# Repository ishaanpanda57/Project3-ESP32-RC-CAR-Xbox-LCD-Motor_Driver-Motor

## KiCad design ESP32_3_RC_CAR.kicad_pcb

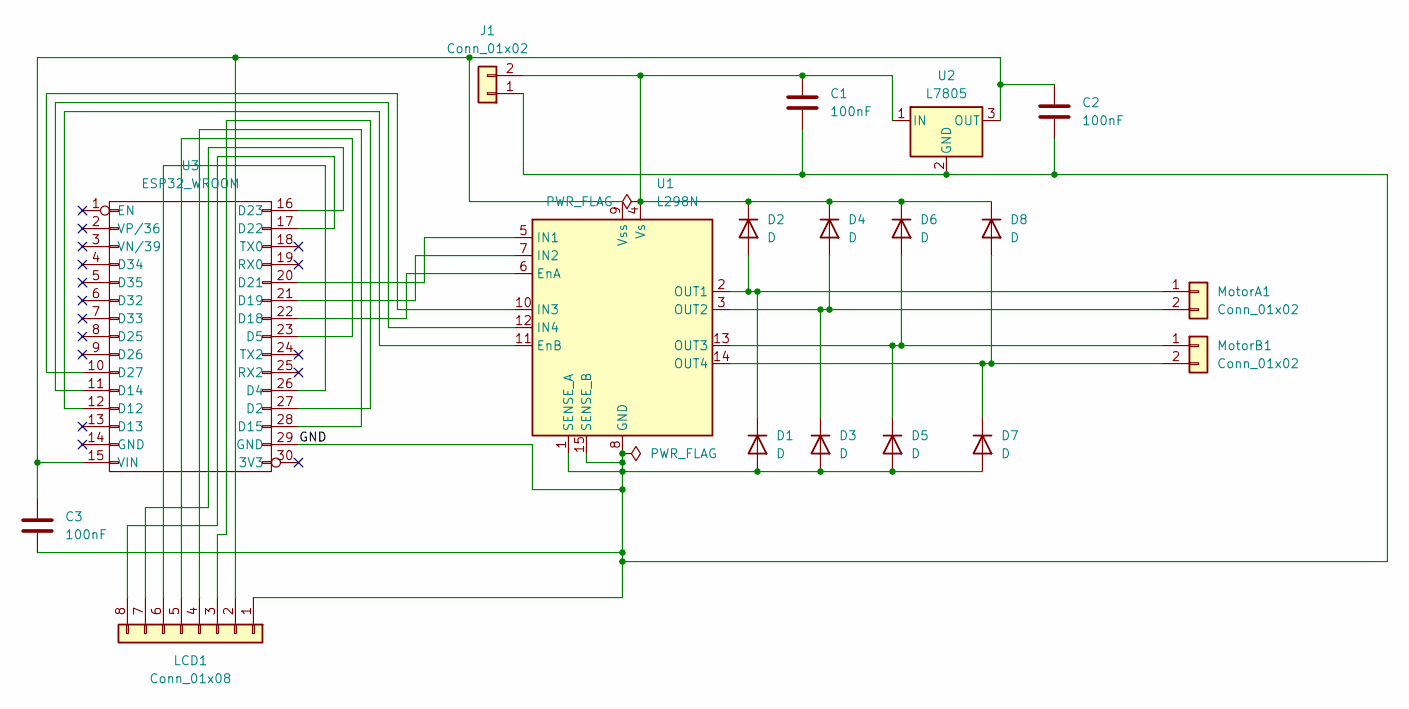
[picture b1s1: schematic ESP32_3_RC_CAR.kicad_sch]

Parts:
C1, C2, C3: 100nF; C_Disc_D3.0mm_W1.6mm_P2.50mm
D1, D2, D3, D4, D5, D6, D7, D8: D; D_DO-41_SOD81_P7.62mm_Horizontal
J1: Conn_01x02; PinHeader_1x02_P2.54mm_Vertical
LCD1: Conn_01x08; PinHeader_1x08_P2.54mm_Vertical
MotorA1: Conn_01x02; PinHeader_1x02_P2.54mm_Vertical
MotorB1: Conn_01x02; PinHeader_1x02_P2.54mm_Vertical
U1: L298N; TO-220-15_P2.54x2.54mm_StaggerEven_Lead5.84mm_TabDown
U2: L7805; TO-220-3_Horizontal_TabDown
U3: ESP32_WROOM; Footprint

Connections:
/GND: C1.2, C2.2, C3.2, D1.2 (A), D3.2 (A), D5.2 (A), D7.2 (A), J1.1, LCD1.1, U1.1 (SENSE_A), U1.8 (GND), U1.15 (SENSE_B), U2.2 (GND), U3.29 (GND)
unnamed: D1.1 (K), D2.2 (A), MotorA1.1, U1.2 (OUT1)
unnamed: C1.1, D2.1 (K), D4.1 (K), D6.1 (K), D8.1 (K), J1.2, U1.4 (Vs), U2.1 (IN)
unnamed: D3.1 (K), D4.2 (A), MotorA1.2, U1.3 (OUT2)
unnamed: D5.1 (K), D6.2 (A), MotorB1.1, U1.13 (OUT3)
unnamed: D7.1 (K), D8.2 (A), MotorB1.2, U1.14 (OUT4)
unnamed: C2.1, C3.1, LCD1.2, U1.9 (Vss), U2.3 (OUT), U3.15 (VIN)
unnamed: LCD1.3, U3.27 (D2)
unnamed: LCD1.4, U3.28 (D15)
unnamed: LCD1.5, U3.23 (D5)
unnamed: LCD1.6, U3.26 (D4)
unnamed: LCD1.7, U3.16 (D23)
unnamed: LCD1.8, U3.17 (D22)
unnamed: U1.6 (EnA), U3.22 (D18)
unnamed: U1.11 (EnB), U3.12 (D12)
unnamed: U1.5 (IN1), U3.20 (D21)
unnamed: U1.7 (IN2), U3.21 (D19)
unnamed: U1.10 (IN3), U3.10 (D27)
unnamed: U1.12 (IN4), U3.11 (D14)

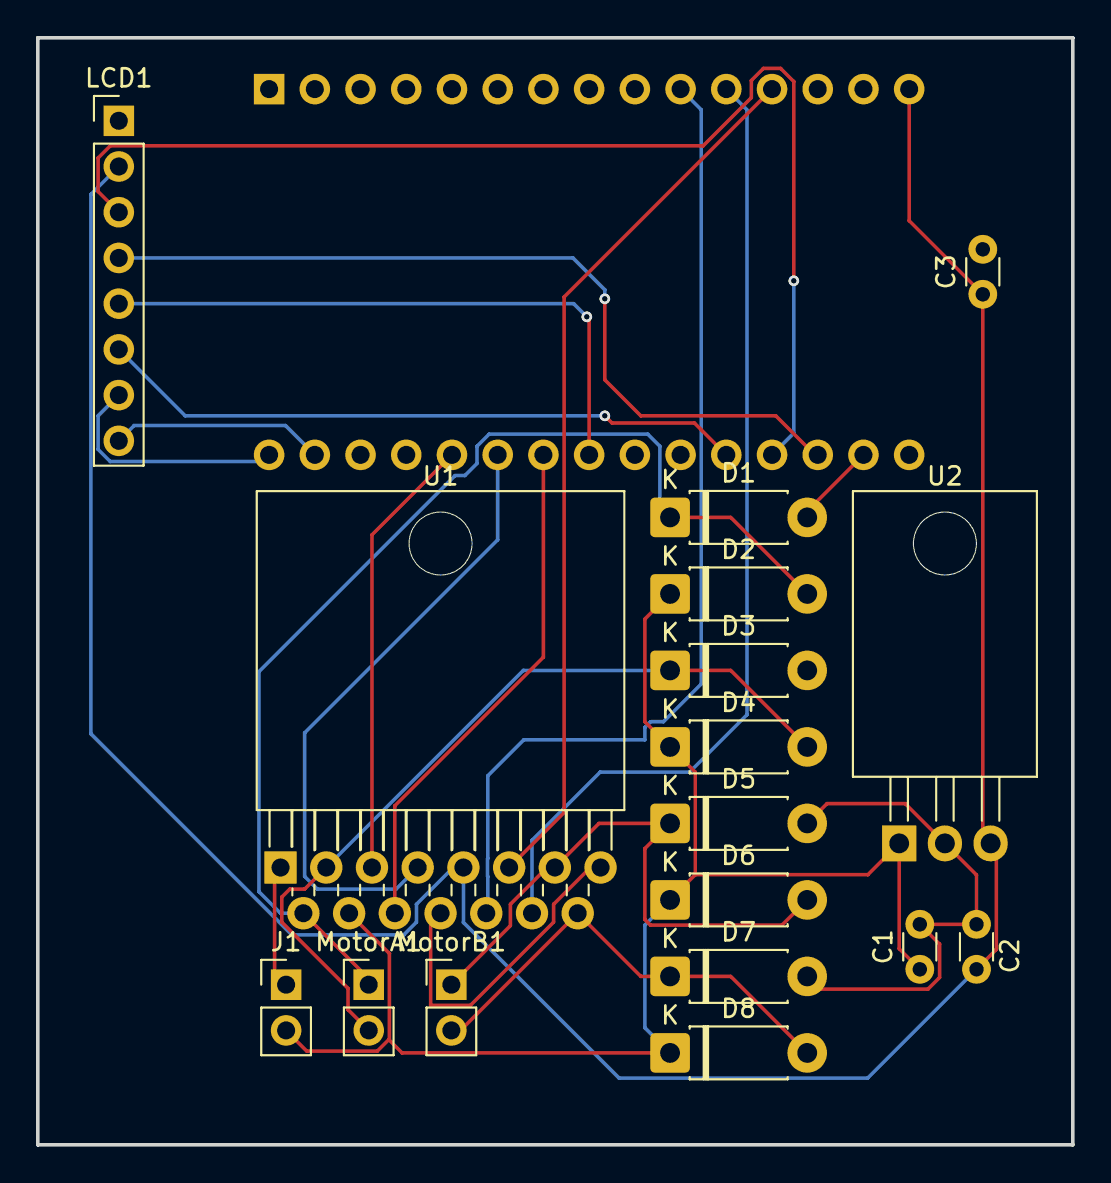
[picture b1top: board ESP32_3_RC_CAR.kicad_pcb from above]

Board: 2 copper layers, 57.5 x 61.5 mm, 18 parts (0 on the bottom side), 19 nets.
